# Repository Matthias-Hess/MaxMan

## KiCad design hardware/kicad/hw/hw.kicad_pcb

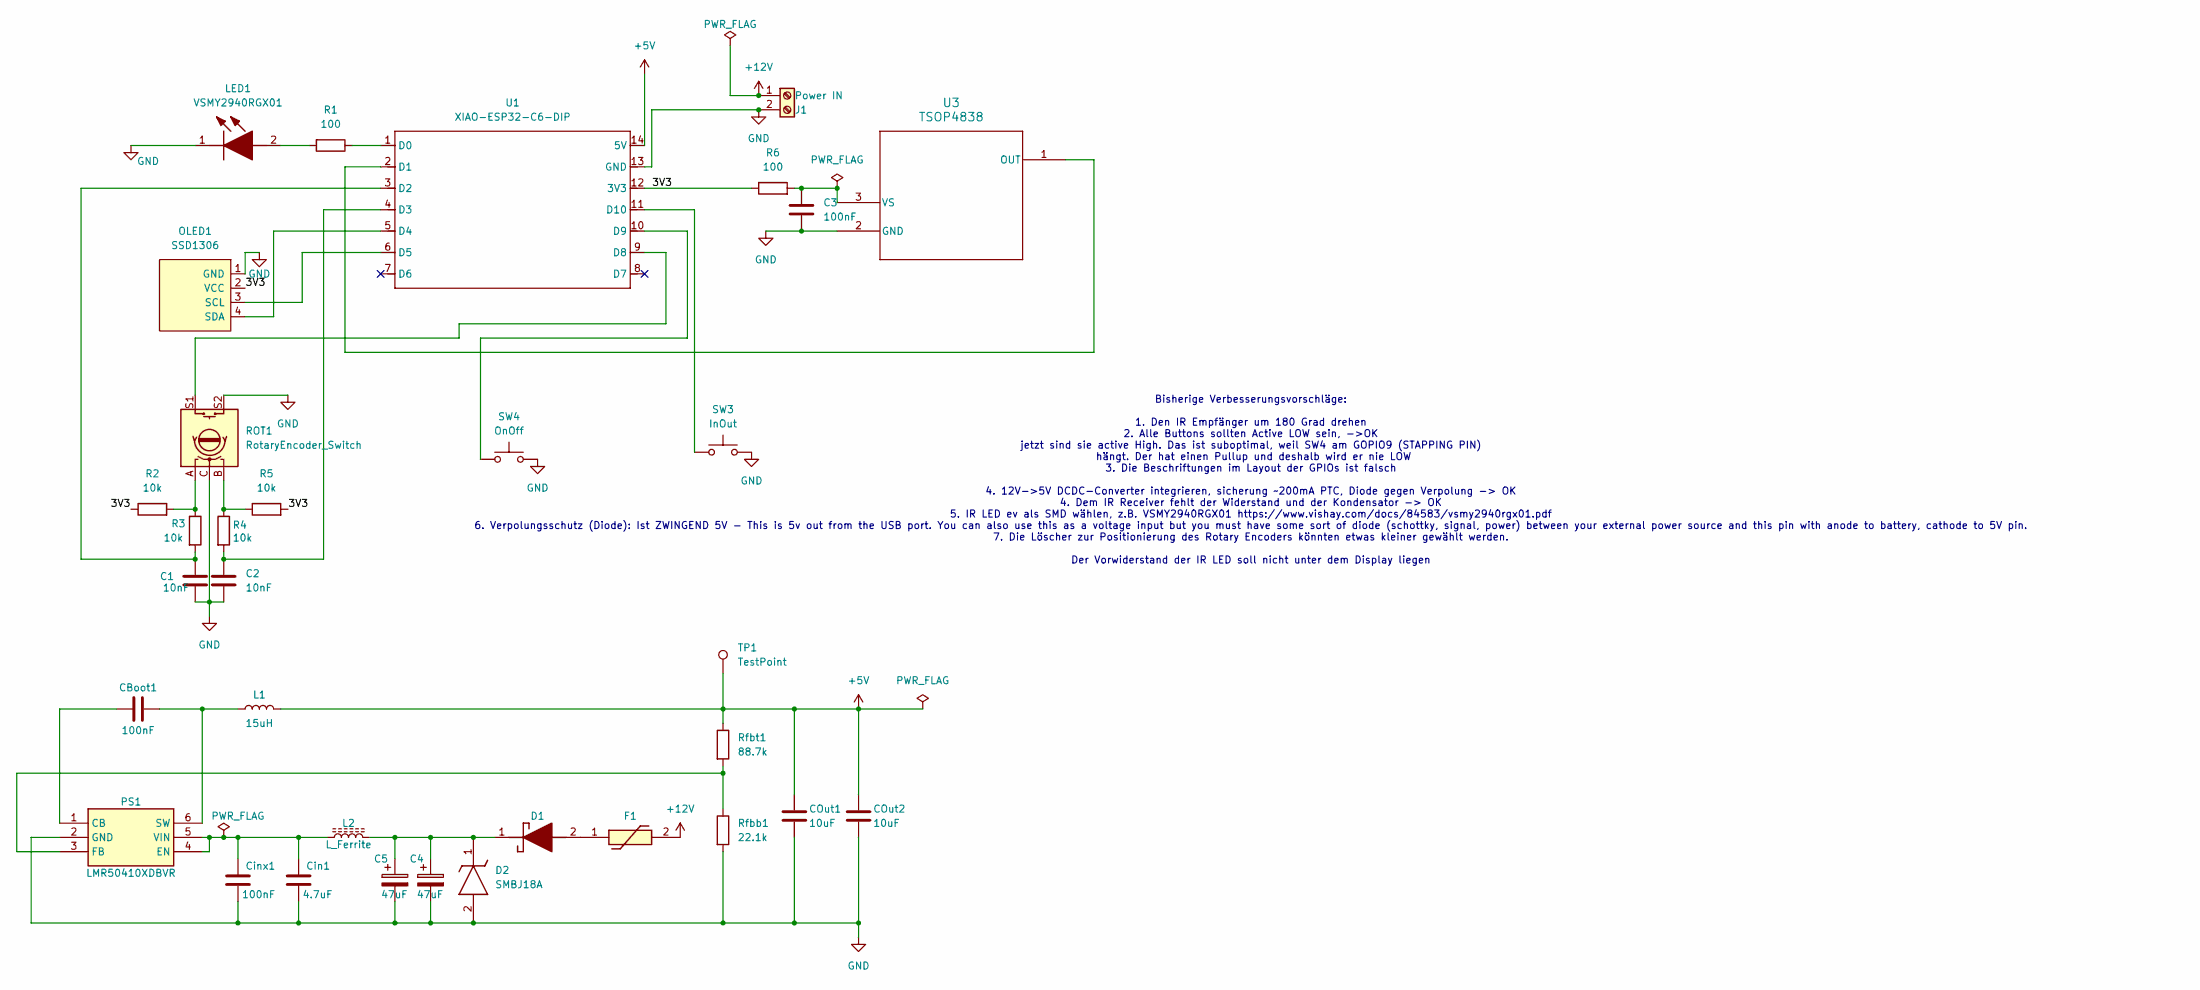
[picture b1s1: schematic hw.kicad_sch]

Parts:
C1, C2: 10nF; C_1206_3216Metric_Pad1.33x1.80mm_HandSolder
C3: 100nF; C_0805_2012Metric
C4, C5: 47uF; CAP_EEEFK1V470P
CBoot1: 100nF; C_0805_2012Metric
COut1, COut2: 10uF; R_0805_2012Metric_Pad1.20x1.40mm_HandSolder
Cin1: 4.7uF; C_0805_2012Metric_Pad1.18x1.45mm_HandSolder
Cinx1: 100nF; C_0805_2012Metric
D1: RB168MM-40TFTR; RB168MM40TFTR; Mouser Part Number 755-RB168MM-40TFTR
D2: SMBJ18A; DIONM5436X261N; Mouser Part Number 576-SMBJ18A
F1: 1206L025_24YR; FUSC3216X100N; Mouser Part Number 576-1206L025/24YR
J1: Power IN; TerminalBlock_Xinya_XY308-2.54-2P_1x02_P2.54mm_Horizontal
L1: 15uH; SRN5040
L2: L_Ferrite; L_1206_3216Metric_Pad1.22x1.90mm_HandSolder
LED1: VSMY2940RGX01; Mouser Part Number 78-VSMY2940RGX01
OLED1: SSD1306; 128x64OLED
PS1: LMR50410XDBVR; SOT95P280X145-6N; Mouser Part Number 595-LMR50410XDBVR
R1, R6: 100; R_1206_3216Metric_Pad1.30x1.75mm_HandSolder
R2, R3, R4, R5: 10k; R_1206_3216Metric_Pad1.30x1.75mm_HandSolder
ROT1: RotaryEncoder_Switch; RotaryEncoder
Rfbb1: 22.1k; R_0805_2012Metric_Pad1.20x1.40mm_HandSolder
Rfbt1: 88.7k; R_0805_2012Metric_Pad1.20x1.40mm_HandSolder
SW3: InOut; SW_TH_Tactile_Omron_B3F-100x
SW4: OnOff; SW_TH_Tactile_Omron_B3F-100x
TP1: TestPoint; TestPoint_Pad_2.0x2.0mm
U1: XIAO-ESP32-C6-DIP; XIAO-ESP32S3-DIP
U3: TSOP4838; TSOP48_VIS

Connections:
+5V: COut1.1, COut2.1, L1.2, Rfbt1.1, TP1.1, U1.14 (5V)
+12V: F1.2, J1.1
/3V3: OLED1.2 (VCC), R2.1, R5.2, R6.1, U1.12 (3V3)
GND: C1.2, C2.2, C3.2, C4.2, C5.2, COut1.2, COut2.2, Cin1.2, Cinx1.2, D2.2 (A), J1.2, LED1.1 (K), OLED1.1 (GND), PS1.2 (GND), ROT1.C, ROT1.S2, Rfbb1.2, SW3.2, SW4.2, U1.13 (GND), U3.2 (GND)
unnamed: D1.2 (A), F1.1
unnamed 5: C4.1, C5.1, D1.1 (K), D2.1 (K), L2.2; also elsewhere on the board
unnamed: LED1.2 (A), R1.2
unnamed: OLED1.3 (SCL), U1.6 (D5)
unnamed: OLED1.4 (SDA), U1.5 (D4)
unnamed: CBoot1.1, PS1.1 (CB)
unnamed: Cin1.1, Cinx1.1, L2.1, PS1.4 (EN), PS1.5 (VIN)
unnamed: PS1.3 (FB), Rfbb1.1, Rfbt1.2
unnamed: CBoot1.2, L1.1, PS1.6 (SW)
unnamed: R2.2, R3.1, ROT1.A
unnamed: R4.1, R5.1, ROT1.B
unnamed: R1.1, U1.1 (D0)
unnamed: U1.2 (D1), U3.1 (OUT)
unnamed: C1.1, R3.2, U1.3 (D2)
unnamed: C2.1, R4.2, U1.4 (D3)
unnamed: ROT1.S1, U1.9 (D8)
unnamed: SW4.1, U1.10 (D9)
unnamed: SW3.1, U1.11 (D10)
unnamed: C3.1, R6.2, U3.3 (VS)

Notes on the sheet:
Bisherige Verbesserungsvorschläge: 1. Den IR Empfänger um 180 Grad drehen 2. Alle Buttons sollten Active LOW sein, ->OK jetzt sind sie active High. Das ist suboptimal, weil SW4 am GOPIO9 (STAPPING PIN) hängt. Der hat einen Pullup und deshalb wird er nie LOW 3. Die Beschriftungen im Layout der GPIOs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

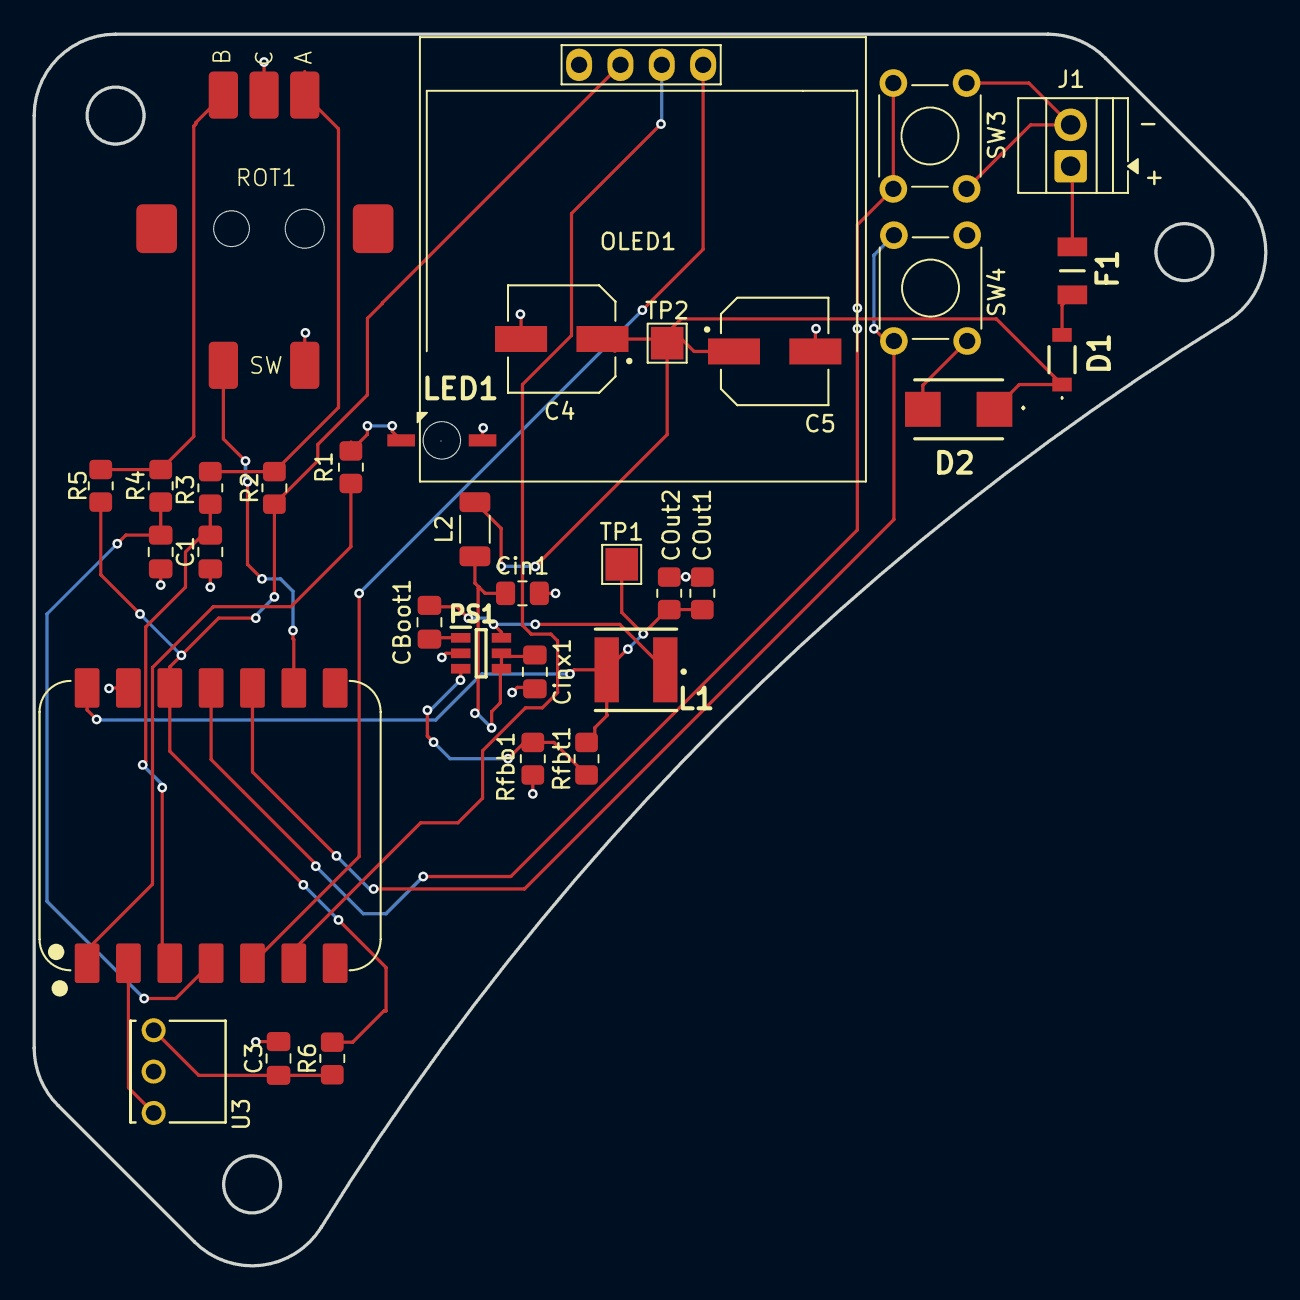
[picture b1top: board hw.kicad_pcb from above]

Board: 2 copper layers, 75.7 x 75.7 mm, 34 parts (0 on the bottom side), 23 nets.

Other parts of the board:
TP2: TestPoint; TestPoint_Pad_2.0x2.0mm

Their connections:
unnamed 5: TP2.1; also elsewhere on the board

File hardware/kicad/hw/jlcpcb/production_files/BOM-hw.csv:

Comment,Designator,Footprint,LCSC,Quantity
47uF,C5,CAP_EEEFK1V470P,,1
LMR50410XDBVR,PS1,SOT95P280X145-6N,,1
10k,R4,R_0805_2012Metric_Pad1.20x1.40mm_HandSolder,,1
100nF,C3,C_0805_2012Metric_Pad1.18x1.45mm_HandSolder,,1
10nF,C2,C_0805_2012Metric_Pad1.18x1.45mm_HandSolder,,1
4.7uF,Cin1,C_0805_2012Metric_Pad1.18x1.45mm_HandSolder,,1
10k,R3,R_0805_2012Metric_Pad1.20x1.40mm_HandSolder,,1
10nF,C1,C_0805_2012Metric_Pad1.18x1.45mm_HandSolder,,1
10k,R5,R_0805_2012Metric_Pad1.20x1.40mm_HandSolder,,1
XIAO-ESP32-C6-DIP,U1,XIAO-ESP32S3-DIP,,1
InOut,SW3,SW_TH_Tactile_Omron_B3F-100x,,1
15uH,L1,SRN5040,,1
Power IN,J1,TerminalBlock_Xinya_XY308-2.54-2P_1x02_P2.54mm_Horizontal,,1
L_Ferrite,L2,L_1206_3216Metric_Pad1.22x1.90mm_HandSolder,,1
88.7k,Rfbt1,R_0805_2012Metric_Pad1.20x1.40mm_HandSolder,,1
100,R6,R_0805_2012Metric_Pad1.20x1.40mm_HandSolder,,1
TSOP4838,U3,TSOP48_VIS,,1
10uF,COut1,R_0805_2012Metric_Pad1.20x1.40mm_HandSolder,,1
SSD1306,OLED1,128x64OLED,,1
RB168MM-40TFTR,D1,RB168MM40TFTR,,1
47uF,C4,CAP_EEEFK1V470P,,1
OnOff,SW4,SW_TH_Tactile_Omron_B3F-100x,,1
TestPoint,TP1,TestPoint_Pad_2.0x2.0mm,,1
VSMY2940RGX01,LED1,VSMY2940RGX01,,1
RotaryEncoder_Switch,ROT1,RotaryEncoder,,1
100nF,CBoot1,C_0805_2012Metric_Pad1.18x1.45mm_HandSolder,,1
SMBJ18A,D2,DIONM5436X261N,,1
1206L025_24YR,F1,FUSC3216X100N,,1
10uF,COut2,R_0805_2012Metric_Pad1.20x1.40mm_HandSolder,,1
10k,R2,R_0805_2012Metric_Pad1.20x1.40mm_HandSolder,,1
100,R1,R_0805_2012Metric_Pad1.20x1.40mm_HandSolder,,1
100nF,Cinx1,C_0805_2012Metric_Pad1.18x1.45mm_HandSolder,,1
22.1k,Rfbb1,R_0805_2012Metric_Pad1.20x1.40mm_HandSolder,,1
TestPoint,TP2,TestPoint_Pad_2.0x2.0mm,,1

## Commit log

2025-03-24 receiver
2025-12-15 some changes
2025-12-15 rotary working in 1 direction
2025-12-17 richtige pins
2025-12-19 eigene implementierung
2025-12-21 refactorings
2025-12-23 new rec
2025-12-24 temp
2025-12-27 checkin
2025-12-28 comm
2025-12-31 test
2026-01-02 Vorwiderstand 100 Ohm
2026-01-03 screendark
2026-01-05 timer
2026-01-05 PIN deklarationen auf Dx geändert
2026-01-05 läuft
2026-02-01 chec
